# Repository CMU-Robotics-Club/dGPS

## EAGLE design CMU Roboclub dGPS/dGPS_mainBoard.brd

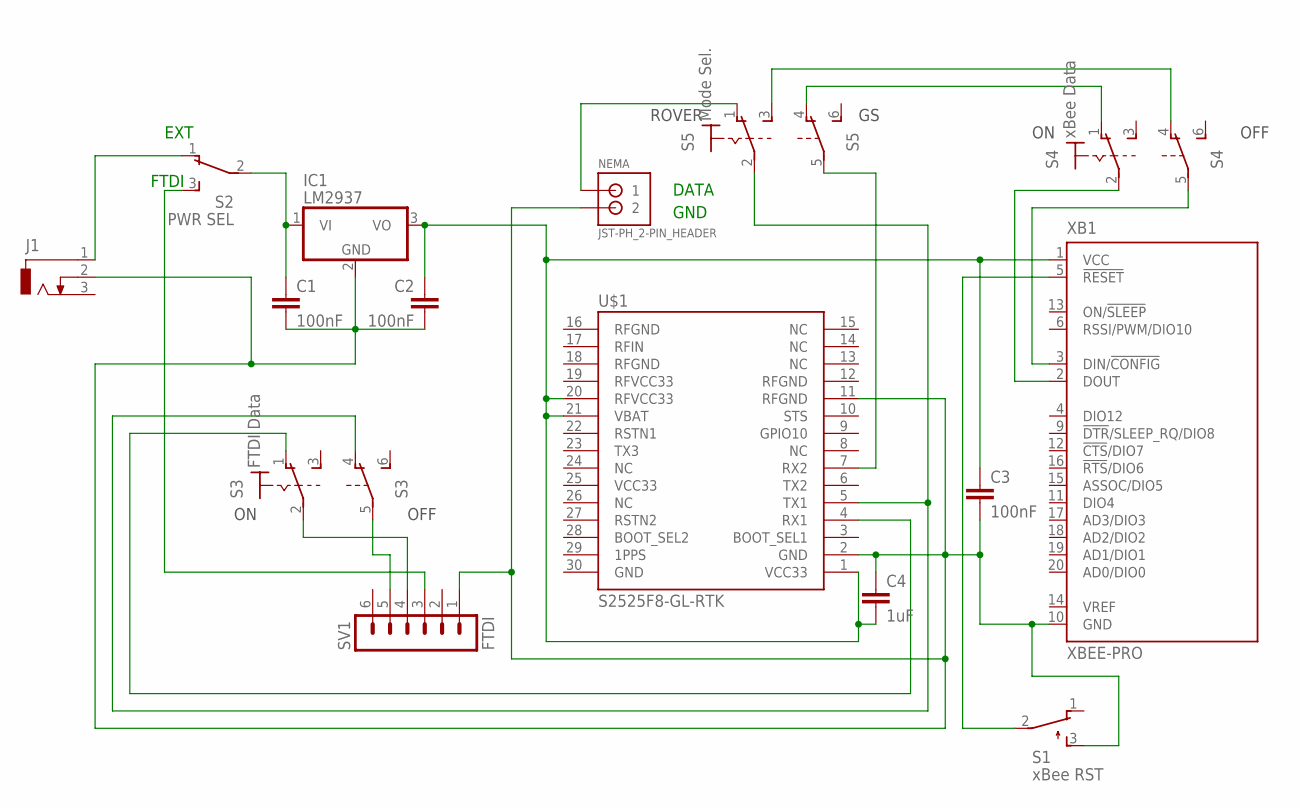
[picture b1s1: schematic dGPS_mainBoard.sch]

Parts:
C1, C2, C3: 100nF; C2.5-5
C4: 1uF; C2.5-5
IC1: LM2937; TO263-3
J1: DCJ0303
NEMA: JST-PH_2-PIN_HEADER; JST_B2B-PH_HEADER
S1: xBee RST; TL3XYO
S2: PWR SEL; TL3XPO
S3: FTDI Data; 320-938
S4: xBee Data; 320-938
S5: Mode Sel.; 320-938
SV1: FTDI; MA06-1
U$1: S2525F8‐GL‐RTK; NS-HP-GL2
XB1: XBEE-PRO

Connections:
unnamed: C2.1, C3.1, C4.2, IC1.3 (VO), U$1.1 (VCC33), U$1.20 (RFVCC33), U$1.21 (VBAT), XB1.1 (VCC)
unnamed: S3.5, SV1.5
unnamed: S5.5, U$1.7 (RX2)
unnamed: S3.1 (O), U$1.4 (RX1)
unnamed: S4.1 (O), S5.4 (O)
unnamed: S4.4 (O), S5.3 (S)
unnamed: NEMA.P1 (1), S5.1 (O)
unnamed: S3.2, SV1.4
unnamed: S3.4 (O), S5.2, U$1.5 (TX1)
unnamed: S4.5, XB1.3 (DIN/!CONFIG)
unnamed: S4.2, XB1.2 (DOUT)
unnamed: C1.2, C2.2, C3.2, C4.1, IC1.2 (GND), J1.2, NEMA.P2 (2), S1.3 (S), SV1.1, U$1.2 (GND), U$1.11 (RFGND), XB1.10 (GND)
unnamed: S1.2, XB1.5 (!RESET)
unnamed: J1.1, S2.1 (O)
unnamed: C1.1, IC1.1 (VI), S2.2
unnamed: S2.3 (S), SV1.3

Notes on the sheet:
ROVER
OFF
GND
DATA
EXT
FTDI

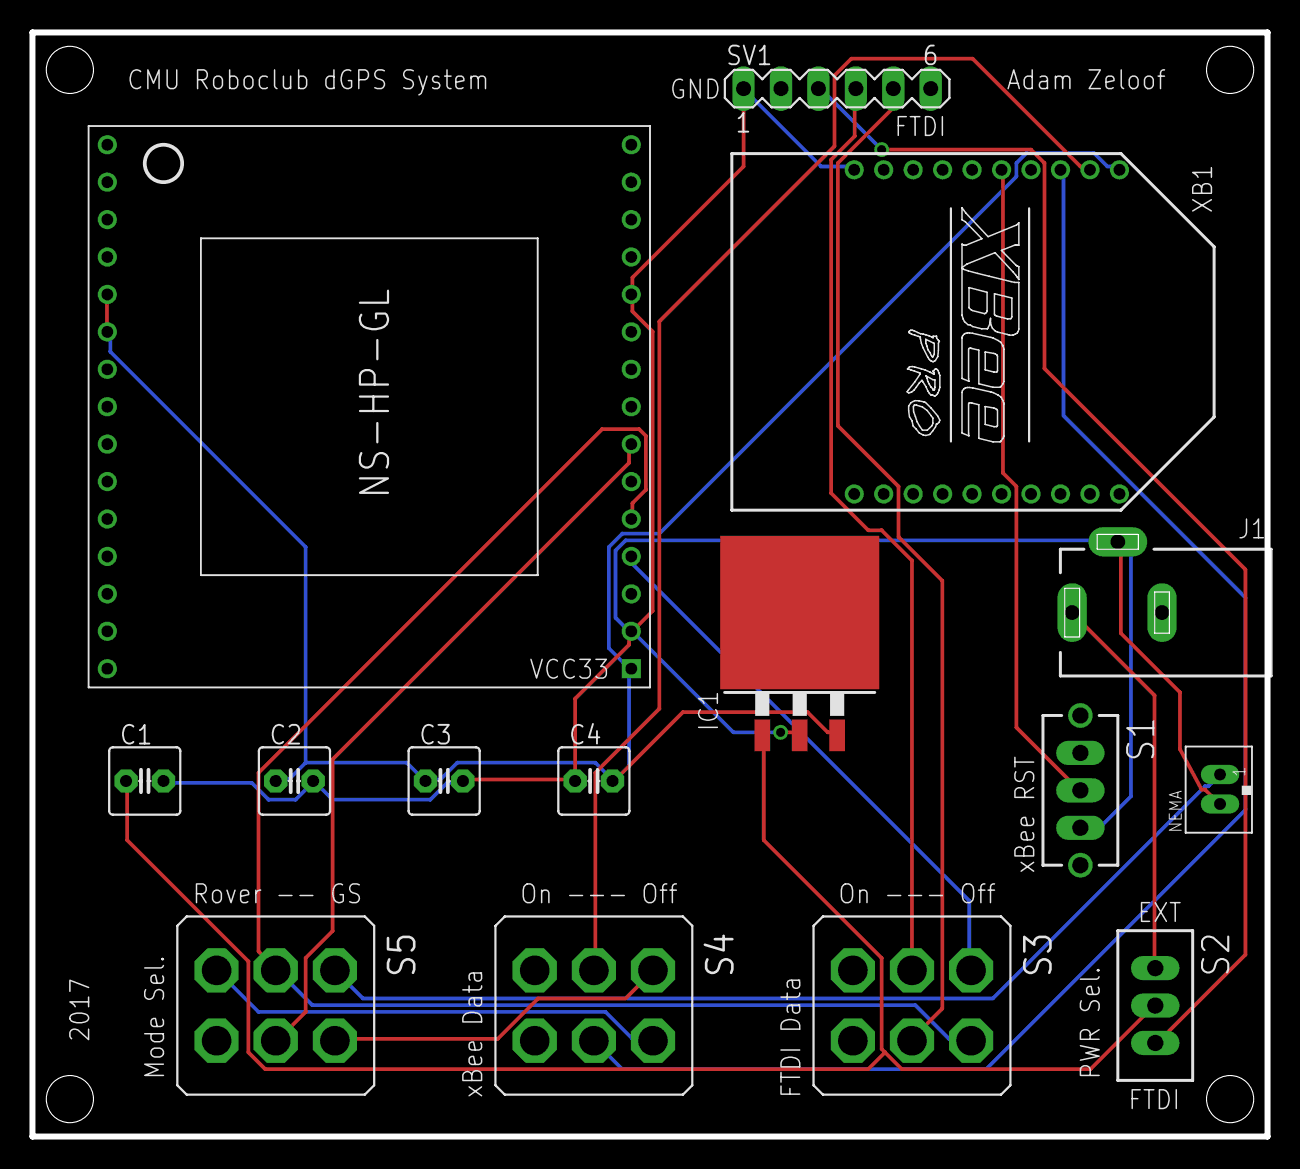
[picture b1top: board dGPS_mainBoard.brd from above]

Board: 2 copper layers, 83.8 x 74.9 mm, 15 parts (0 on the bottom side), 16 nets.

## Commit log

2017-04-15 Schematic & Board Layout
2017-04-15 board
2017-04-24 Added decoupling caps, updated board layout
2017-04-25 Changed several things
2017-04-26 Changed many things
2017-04-26 Added indicator LEDs and did other stuff
2017-04-26 Minor routing fixes
